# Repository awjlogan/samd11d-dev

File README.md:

# SAMD1x-DEV

A minimal breakout board for the [Microchip (Atmel) ATSAMD11D][atsamd11] Cortex-M0+ based microcontroller. All pins are broken out to standard 2.54 mm (0.1 in) headers.

All design files and source code are under the [_Don't Be A Dick_][dbad-github] license.

## Hardware

PCBs were designed with KiCad 5; all files are provided and no custom KiCad parts are required. Most components are surface mount, with all passives being 0603 sized. Note that due to the part density, there are no reference designators on the top silkscreen.

A full bill of materials with order codes for Farnell and Mouser is included.

## Change Notes

### v0.1 -> v0.21

 - [X] Use USB-B with mounting pegs rather than pure SMD.
 - [X] Add graphical notch on programming header space.
 - [X] Choose a more widely available button (C&K KMR2).
 - [X] Increase LED limiting resistor values.
 - [X] Move LEDs off PA02 and PA04 as these are useful for ADC/DAC, now on PA14/15.
 - [X] Remove LED on PA03, just have ADC reference decoupling.
 - [X] Add power indication LED on 3V3.
 - [X] Move switch onto pin with fewer alt functions (PA16).
 - [X] Add additional switch (PA22).

[atsamd11]: https://www.microchip.com/wwwproducts/en/ATSAMD11D14
[dbad-github]: https://github.com/philsturgeon/dbad

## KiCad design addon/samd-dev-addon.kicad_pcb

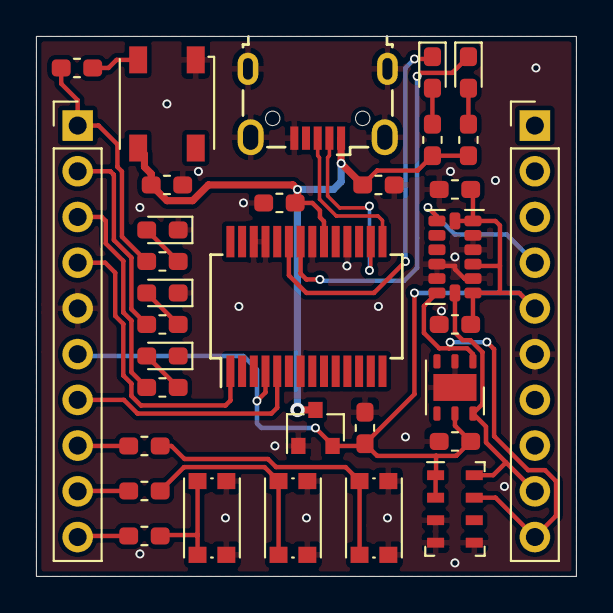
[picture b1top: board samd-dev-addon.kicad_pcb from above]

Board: 2 copper layers, 30.0 x 30.0 mm, 33 parts (0 on the bottom side), 27 nets.

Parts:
C1, C2: 2u2; C_0603_1608Metric_Pad1.05x0.95mm_HandSolder
C3, C4, C5, C6, C7: 100n; C_0603_1608Metric_Pad1.05x0.95mm_HandSolder
D1, D2, D4, D5, D6: LED; LED_0603_1608Metric_Pad1.05x0.95mm_HandSolder
D3: Inolux_IN-PI554FCH; LED_Inolux_IN-PI554FCH_PLCC4_5.0x5.0mm_P3.2mm
J1: USB_B_Micro; USB_Micro-B_Wuerth_629105150521
J2, J3: Conn_01x10; PinHeader_1x10_P2.54mm_Vertical
R1, R2, R3, R4, R5, R6, R7, R8, R9: 330R; R_0603_1608Metric_Pad1.05x0.95mm_HandSolder
SW1, SW2, SW3: SW_Push; SW_Push_1P1T_NO_CK_KMR2
U1: MCP1700-3302E_SOT23; SOT-23
U2: FT232RL; SSOP-28_5.3x10.2mm_P0.65mm
U3: Si7020-A20; DFN-6-1EP_3x3mm_P1mm_EP1.5x2.4mm
U4: ADXL343; LGA-14_3x5mm_P0.8mm_LayoutBorder1x6y
U5: MS5607-02BA; LGA-8_3x5mm_P1.25mm

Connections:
+3V3: C2.1, C3.1, C4.1, C6.1, J2.6, J3.5, U1.2, U2.4, U3.5, U4.1, U4.3, U4.6, U4.7, U5.1, U5.2
+5V: C1.1, C5.1, C7.1, D3.3, J1.1, R1.1, R2.1, U1.3, U2.20
/D+: J1.3, U2.15
/D-: J1.2, U2.16
/PA02: J3.4, U4.8
/PA05: J2.10, R3.2
/PA06: J2.9, R4.2
/PA07: J2.8, R5.2
/PA08: J2.7, U2.5
/PA09: J2.4, U2.1
/PA14: J2.3, R7.2
/PA15: J2.2, R8.2
/PA16: J2.1, R6.1, R9.2
/PA22: J3.10, U3.1, U4.13, U5.7
/PA23: J3.9, U3.6, U4.14, U5.8
/RXLED: D2.1, U2.22
/TXLED: D1.1, U2.23
GND: C1.2, C2.2, C3.2, C4.2, C5.2, C6.2, C7.2, D3.1, D4.1, D5.1, D6.1, J1.5, J1.6, J2.5, J3.6, SW1.2, SW2.2, SW3.2, U1.1, U2.7, U2.18, U2.21, U2.25, U2.26, U3.2, U3.7, U4.2, U4.4, U4.5, U4.11, U4.12, U5.3, U5.4, U5.5
unnamed: D1.2, R1.2
unnamed: D2.2, R2.2
unnamed: D3.2, R6.2
unnamed: D4.2, R7.1
unnamed: D5.2, R8.1
unnamed: D6.2, R9.1
unnamed: R3.1, SW1.1
unnamed: R4.1, SW2.1
unnamed: R5.1, SW3.1

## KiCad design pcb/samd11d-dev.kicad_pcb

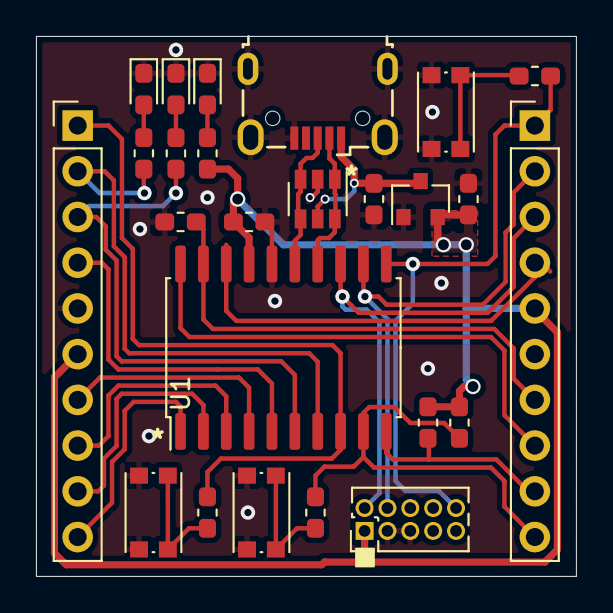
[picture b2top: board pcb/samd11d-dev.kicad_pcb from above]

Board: 2 copper layers, 30.0 x 30.0 mm, 25 parts (0 on the bottom side), 27 nets.

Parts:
C3, C4: 4u7; C_0603_1608Metric_Pad1.05x0.95mm_HandSolder
C5, C6: 100n; C_0603_1608Metric_Pad1.05x0.95mm_HandSolder
D1, D2, D3: LED; LED_0603_1608Metric_Pad1.05x0.95mm_HandSolder
J1: Conn_02x05_Odd_Even; PinHeader_2x05_P1.27mm_Vertical
J2: USB_B_Micro; USB_Micro-B_Wuerth_629105150521
J3, J4: Conn_01x10; PinHeader_1x10_P2.54mm_Vertical
R1, R2: 4K7; R_0603_1608Metric_Pad1.05x0.95mm_HandSolder
R3, R4, R5, R6, R7, R8: 330R; R_0603_1608Metric_Pad1.05x0.95mm_HandSolder
SW1, SW2, SW3: SW_Push; SW_Push_1P1T_NO_CK_KMR2
U1: ATSAMD11D14A-SS; SOIC-20W_7.5x12.8mm_P1.27mm
U3: MCP1700-3302E_SOT23; SOT-23
U4: USBLC6-2SC6; SOT-23-6

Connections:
+3V3: C4.2, C5.2, J1.1, J3.6, J4.5, R1.2, R2.2, R4.1, U1.17, U3.2
/PA02: J4.4, U1.18
/PA03: C6.2, J4.7, U1.19
/PA04: J4.8, U1.20
/PA05: J3.10, U1.1
/PA06: J3.9, U1.2
/PA07: J3.8, U1.3
/PA08: J3.7, U1.4
/PA09: J3.4, U1.5
/PA14: J3.3, R5.1, U1.6
/PA15: J3.2, R3.1, U1.7
/PA16: J3.1, R7.2, U1.8
/PA22: J4.10, R1.1, R8.2, U1.9
/PA23: J4.9, R2.1, U1.10
/PA30: J1.4, J4.2, U1.12
/PA31: J1.2, J4.3, U1.13
/USB_D+: J2.3, U1.15, U4.3, U4.4
/USB_D-: J2.2, U1.14, U4.1, U4.6
/~RST: J1.10, J4.1, R6.2, U1.11
GND: C3.1, C4.1, C5.1, C6.1, D1.1, D2.1, D3.1, J1.3, J1.5, J2.5, J2.6, J3.5, J4.6, SW1.2, SW2.2, SW3.2, U1.16, U3.1, U4.2
unnamed: D1.2, R3.2
unnamed: D2.2, R5.2
unnamed: D3.2, R4.2
unnamed: R6.1, SW1.1
unnamed: R7.1, SW2.1
unnamed: R8.1, SW3.1
VBUS: C3.2, J2.1, U3.3, U4.5

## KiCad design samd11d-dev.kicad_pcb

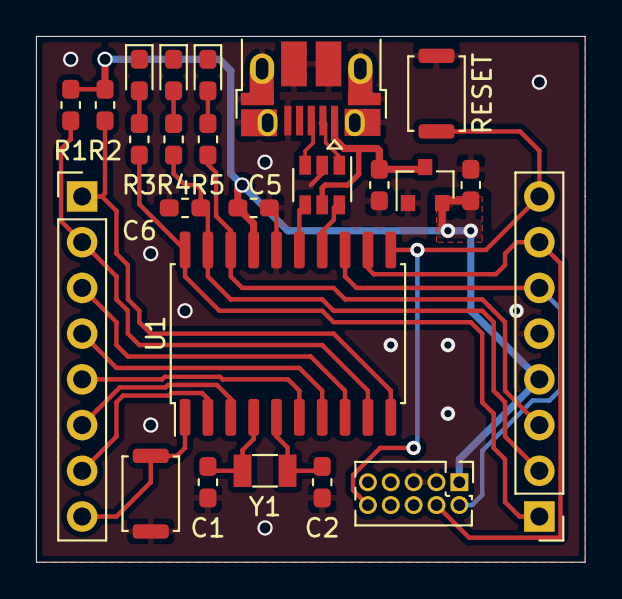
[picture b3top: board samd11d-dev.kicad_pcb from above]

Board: 2 copper layers, 30.5 x 29.2 mm, 24 parts (0 on the bottom side), 26 nets.

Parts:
C1, C2: 15p; C_0603_1608Metric_Pad1.05x0.95mm_HandSolder
C3, C4: 4u7; C_0603_1608Metric_Pad1.05x0.95mm_HandSolder
C5, C6: 100n; C_0603_1608Metric_Pad1.05x0.95mm_HandSolder
D1, D2, D3: LED; LED_0603_1608Metric_Pad1.05x0.95mm_HandSolder
J1: Conn_02x05_Odd_Even; PinHeader_2x05_P1.27mm_Vertical
J2: USB_B_Micro; USB_Micro-B_Amphenol_10103594-0001LF_Horizontal
J3, J4: Conn_01x08; PinHeader_1x08_P2.54mm_Vertical
R1, R2: 4K7; R_0603_1608Metric_Pad1.05x0.95mm_HandSolder
R3, R4, R5: 180R; R_0603_1608Metric_Pad1.05x0.95mm_HandSolder
RESET: SW_Push; SW_Push_SPST_NO_Alps_SKRK
SW2: SW_Push; SW_Push_SPST_NO_Alps_SKRK
U1: ATSAMD11D14A-SS; SOIC-20W_7.5x12.8mm_P1.27mm
U3: MCP1700-3302E_SOT23; SOT-23
U4: USBLC6-2SC6; SOT-23-6
Y1: 32.768 kHz; Crystal_SMD_3215-2Pin_3.2x1.5mm

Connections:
+3V3: C4.2, C5.2, J1.1, J4.4, R1.2, R2.2, U1.17, U3.2
/PA02: J4.3, R5.1, U1.18
/PA03: C6.2, J4.2, R4.1, U1.19
/PA04: J4.1, R3.1, U1.20
/PA05: J3.8, SW2.1, U1.1
/PA06: J3.7, U1.2
/PA07: J3.6, U1.3
/PA14: J3.5, U1.6
/PA15: J3.4, U1.7
/PA16: J3.3, U1.8
/PA22: J3.2, R1.1, U1.9
/PA23: J3.1, R2.1, U1.10
/PA30: J1.4, J4.7, U1.12
/PA31: J1.2, J4.6, U1.13
/USB_D+: J2.3, U4.3
/USB_D-: J2.2, U4.1
/USB_ESD_D+: U1.15, U4.4
/USB_ESD_D-: U1.14, U4.6
/~RST: J1.10, J4.8, RESET.1, U1.11
GND: C1.2, C2.2, C3.1, C4.1, C5.1, C6.1, D1.1, D2.1, D3.1, J1.3, J1.5, J2.5, J2.6, J4.5, RESET.2, SW2.2, U1.16, U3.1, U4.2
unnamed: C1.1, U1.4, Y1.1
unnamed: C2.1, U1.5, Y1.2
unnamed: D1.2, R3.2
unnamed: D2.2, R4.2
unnamed: D3.2, R5.2
VBUS: C3.2, J2.1, U3.3, U4.5

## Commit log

2020-02-19 First public release
2020-02-19 Add pcb folder
2020-02-20 Added some bits to README
2020-06-03 Add some todo notes after building the first one
2020-06-03 Update feature template
2020-06-07 Version 0.2 changes. Include schematic PDF and PNG of rendered board
2020-06-07 Missed semicolon
2020-06-07 Remove unused sections
2020-06-07 Add picture
2020-06-07 Wrong bracket type
2020-11-06 Complete new layout for v0.21
2020-11-10 Sensor add on board commit
2020-11-23 v2.1 manufactured
2020-11-23 Add base files for examples
2020-11-26 base files
2020-11-29 Move common functions out
2020-11-29 Unique ID fetching
2020-12-04 Working unique ID example, and refactor register assignments
2020-12-04 Add (c) notice
2020-12-04 Light up LEDs
2020-12-04 Start internal temperature measurement example
2020-12-07 Move computer
2020-12-08 Change name in Atmel Studio
2020-12-10 Add TSEN
2020-12-11 Working crude temperature sensor
2020-12-13 Add blinking LED example
